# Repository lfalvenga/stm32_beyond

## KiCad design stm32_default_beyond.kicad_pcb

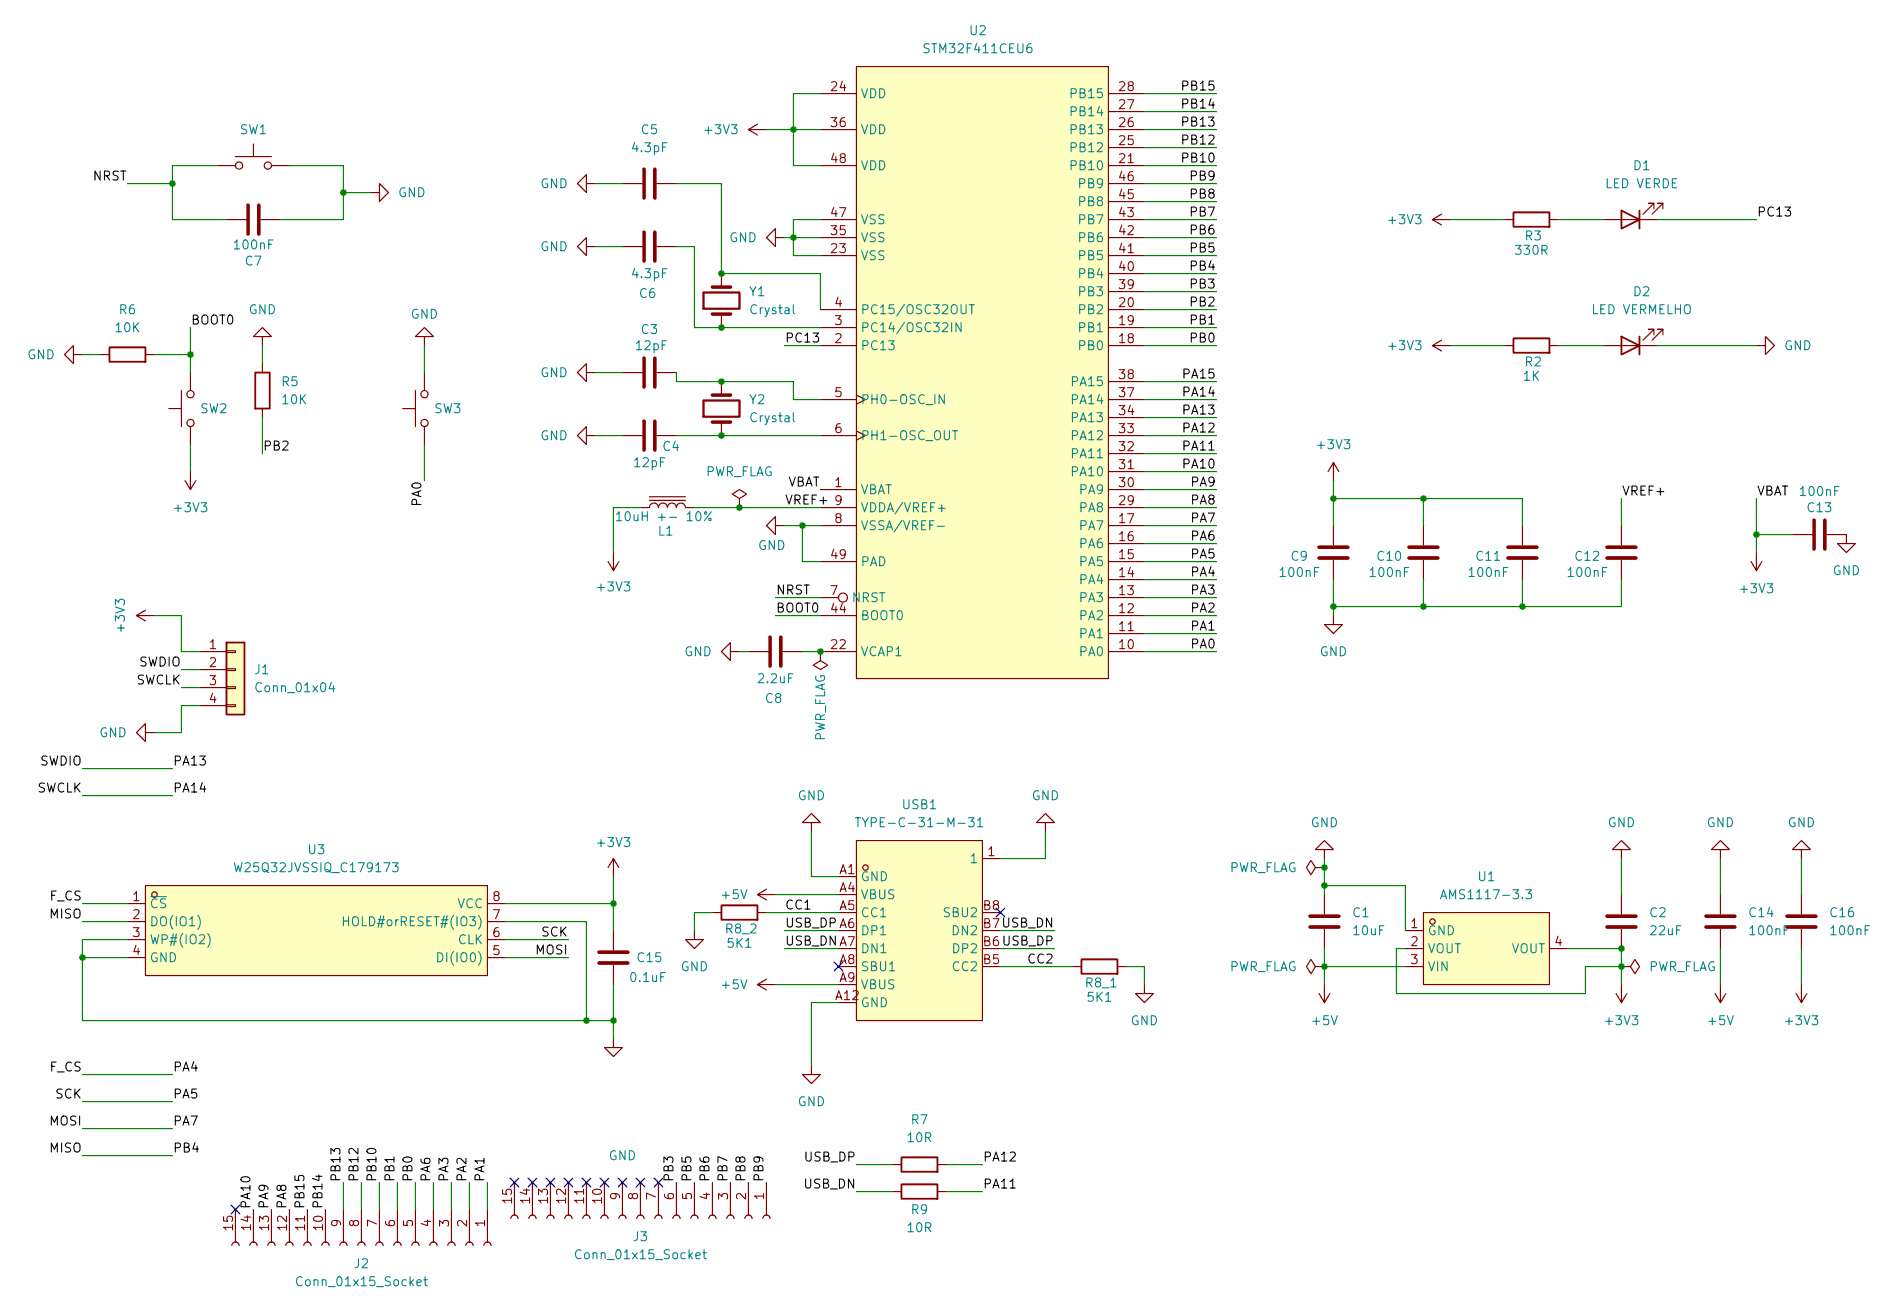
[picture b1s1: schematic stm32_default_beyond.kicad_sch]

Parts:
C1: 10uF; C_0805_2012Metric; LCSC Part C15850
C2: 22uF; C_0805_2012Metric; LCSC Part C45783
C3, C4: 12pF; C_0402_1005Metric; LCSC Part C1547
C5, C6: 4.3pF; C_0201_0603Metric; LCSC Part C20069223
C7, C9, C10, C11, C12, C13, C14, C16: 100nF; C_0402_1005Metric; LCSC Part C1525
C8: 2.2uF; C_0603_1608Metric; LCSC Part C23630
C15: 0.1uF; C_0402_1005Metric; LCSC Part C1525
D1: LED VERDE; LED_0805_2012Metric; LCSC Part C2297
D2: LED VERMELHO; LED_0603_1608Metric; LCSC Part C2286
J1: Conn_01x04; PinSocket_1x04_P2.54mm_Horizontal
J2, J3: Conn_01x15_Socket; PinHeader_1x15_P2.54mm_Vertical
L1: 10uH +- 10%; L_1210_3225Metric; LCSC Part C90321
R2: 1K; R_0603_1608Metric; LCSC Part C21190
R3: 330R; R_0805_2012Metric; LCSC Part C17630
R5, R6: 10K; R_0603_1608Metric; LCSC Part C25804
R7, R9: 10R; R_1206_3216Metric; LCSC Part C17903
R8_1, R8_2: 5K1; R_0603_1608Metric; LCSC Part C23186
SW1, SW2, SW3: SW-SMD_L3.9-W3.0-P4.45; LCSC Part C720477
U1: AMS1117-3.3; SOT-223-3_L6.5-W3.4-P2.30-LS7.0-BR; MPN AMS1117-3.3; LCSC Part C6186
U2: STM32F411CEU6; UFQFPN-48_L7.0-W7.0-P0.50-BL-EP; MPN STM32F411CEU6; LCSC Part C60420
U3: W25Q32JVSSIQ_C179173; SOIC-8_L5.3-W5.3-P1.27-LS8.0-BL; MPN W25Q32JVSSIQ; LCSC Part C179173
USB1: TYPE-C-31-M-31; USB-C-SMD_TYPE-C-31-M-31; MPN TYPE-C-31-M-31; LCSC Part C2760486
Y1, Y2: Crystal; Crystal_SMD_3215-2Pin_3.2x1.5mm; LCSC Part C49329916

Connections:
+3V3: C2.2, C9.1, C10.1, C11.1, C13.1, C15.2, C16.2, J1.1, L1.1, R2.1, R3.1, SW2.1, U1.2 (VOUT), U1.4 (VOUT), U2.1 (VBAT), U2.24 (VDD), U2.36 (VDD), U2.48 (VDD), U3.8 (VCC)
+5V: C1.2, C14.2, U1.3 (VIN), USB1.A4 (VBUS), USB1.A9 (VBUS)
/<NO NET>: U2.38 (PA15)
/BOOT0: R6.2, SW2.2, U2.44 (BOOT0)
/CC1: R8_2.2, USB1.A5 (CC1)
/CC2: R8_1.1, USB1.B5 (CC2)
/F_CS: U2.14 (PA4), U3.1 (~CS)
/MISO: U2.40 (PB4), U3.2 (DO(IO1))
/MOSI: U2.17 (PA7), U3.5 (DI(IO0))
/NRST: C7.1, SW1.1, U2.7 (NRST)
/PA0: SW3.1, U2.10 (PA0)
/PA1: J2.1, U2.11 (PA1)
/PA2: J2.2, U2.12 (PA2)
/PA3: J2.3, U2.13 (PA3)
/PA5: U2.15 (PA5), U3.6 (CLK)
/PA6: J2.4, U2.16 (PA6)
/PA8: J2.12, U2.29 (PA8)
/PA9: J2.13, U2.30 (PA9)
/PA10: J2.14, U2.31 (PA10)
/PA11: R9.2, U2.32 (PA11)
/PA12: R7.2, U2.33 (PA12)
/PA13: J1.2, U2.34 (PA13)
/PA14: J1.3, U2.37 (PA14)
/PB0: J2.5, U2.18 (PB0)
/PB1: J2.6, U2.19 (PB1)
/PB2: R5.2, U2.20 (PB2)
/PB3: J3.6, U2.39 (PB3)
/PB5: J3.5, U2.41 (PB5)
/PB6: J3.4, U2.42 (PB6)
/PB7: J3.3, U2.43 (PB7)
/PB8: J3.2, U2.45 (PB8)
/PB9: J3.1, U2.46 (PB9)
/PB10: J2.7, U2.21 (PB10)
/PB12: J2.8, U2.25 (PB12)
/PB13: J2.9, U2.26 (PB13)
/PB14: J2.10, U2.27 (PB14)
/PB15: J2.11, U2.28 (PB15)
/PC13: D1.1 (K), U2.2 (PC13)
/USB_DN: R9.1, USB1.A7 (DN1), USB1.B7 (DN2)
/USB_DP: R7.1, USB1.A6 (DP1), USB1.B6 (DP2)
/VREF+: C12.1, L1.2, U2.9 (VDDA/VREF+)
GND: C1.1, C2.1, C3.2, C4.1, C5.2, C6.1, C7.2, C8.1, C9.2, C10.2, C11.2, C12.2, C13.2, C14.1, C15.1, C16.1, D2.1 (K), J1.4, R5.1, R6.1, R8_1.2, R8_2.1, SW1.2, SW3.2, U1.1 (GND), U2.8 (VSSA/VREF-), U2.23 (VSS), U2.35 (VSS), U2.47 (VSS), U2.49 (PAD), U3.3 (WP#(IO2)), U3.4 (GND), U3.7 (HOLD#orRESET#(IO3)), USB1.1, USB1.A1 (GND), USB1.A12 (GND)
unnamed: D1.2 (A), R3.2
unnamed: D2.2 (A), R2.2
unnamed: C6.2, U2.3 (PC14/OSC32IN), Y1.1
unnamed: C5.1, U2.4 (PC15/OSC32OUT), Y1.2
unnamed: C3.1, U2.5 (PH0-OSC_IN), Y2.2
unnamed: C4.2, U2.6 (PH1-OSC_OUT), Y2.1
unnamed: C8.2, U2.22 (VCAP1)

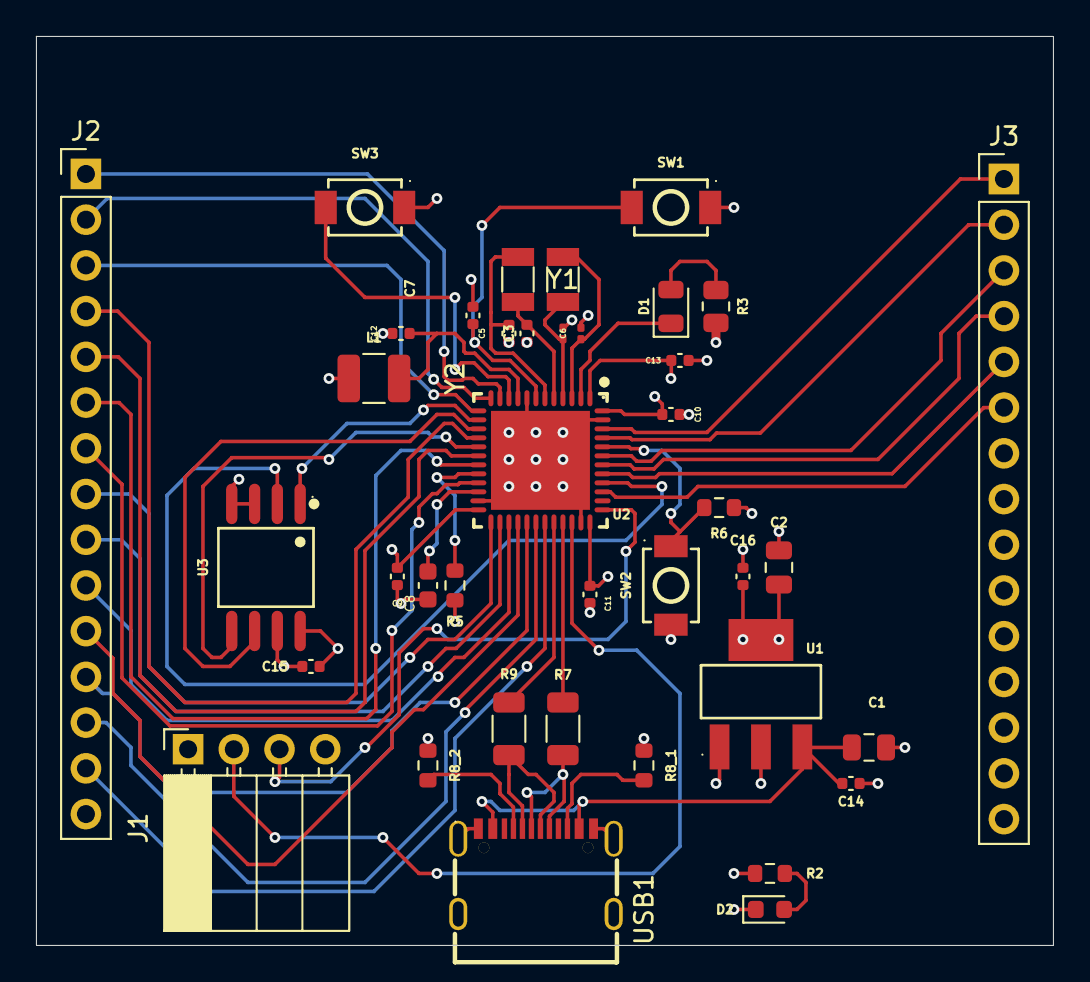
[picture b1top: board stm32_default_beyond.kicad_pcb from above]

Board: 4 copper layers, 56.5 x 50.5 mm, 39 parts (0 on the bottom side), 48 nets.
